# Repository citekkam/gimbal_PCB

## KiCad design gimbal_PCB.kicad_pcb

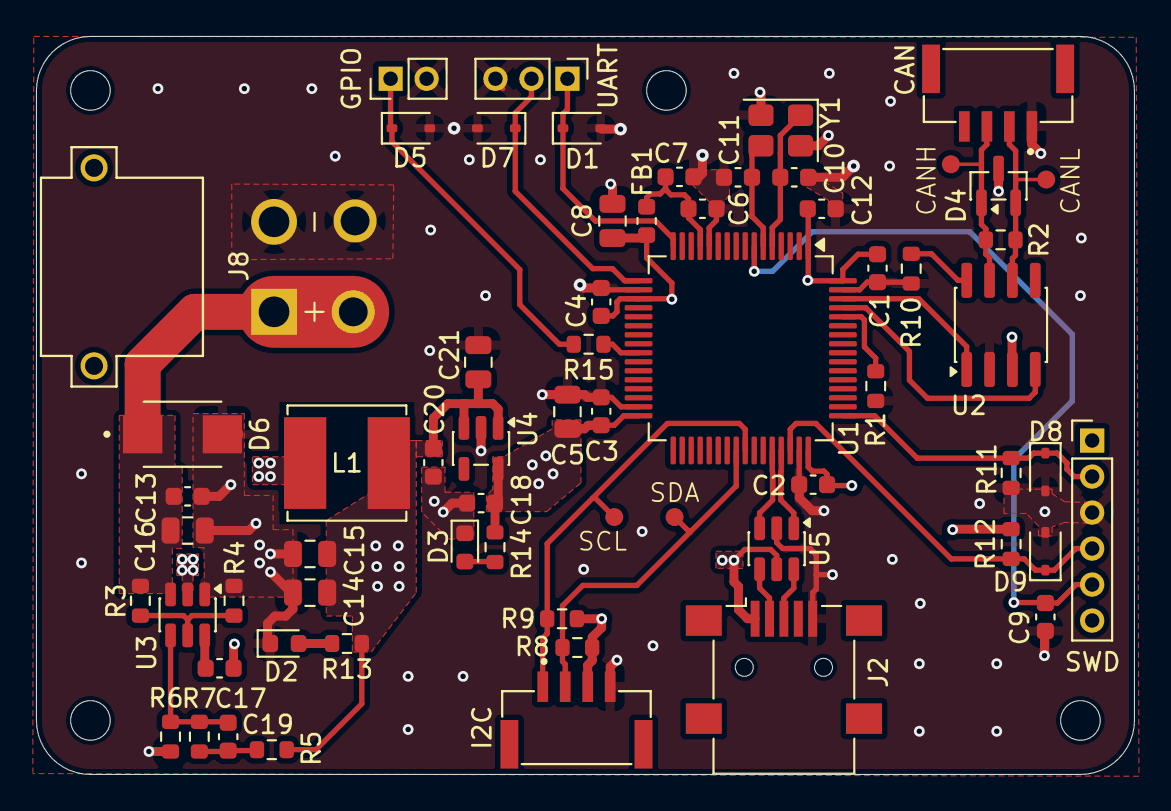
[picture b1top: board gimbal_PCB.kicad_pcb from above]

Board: 4 copper layers, 61.0 x 41.0 mm, 70 parts (0 on the bottom side), 33 nets.

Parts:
C1, C2, C3, C4, C9, C12: 100n; C_0603_1608Metric
C5, C16: 10u; C_0805_2012Metric
C6: 10n; C_0603_1608Metric
C7, C18, C20: 1u; C_0603_1608Metric
C8: 1u; C_0805_2012Metric
C10, C11: 8p; C_0603_1608Metric
C13, C17: 0.1u; C_0603_1608Metric
C14, C15: 22u; C_0805_2012Metric
C19: 75p; C_0603_1608Metric
C21: 1m; C_0805_2012Metric
CAN: Conn_01x04_Socket; JST_SM04B-GHS-TB_LF__SN_-
CANH: Conn_01x01_Pin; Test_point
CANL: Conn_01x01_Pin; Test_point
D1, D5, D7, D8, D9: PESD5V0S1UL; D_SOD-323
D2, D3: LED; LED_0603_1608Metric
D4: NUP2105L; SOT-23
D6: SMBJ28A; DIOM5436X244N
FB1: 120R; L_0603_1608Metric
GPIO: Conn_01x02_Pin; PinHeader_1x02_P2.00mm_Vertical
H3, H4, H5, H6: MountingHole; MountingHole_2.2mm_M2
I2C: Conn_01x04_Socket; JST_SM04B-GHS-TB_LF__SN_-
J2: USB_B_Mini; USB_Mini-B_Lumberg_2486_01_Horizontal
J5, J9: Conn_01x01_Socket; ODrive_PAD
J8: XT30PW-M; AMASS_XT30PW-M
L1: 10u; L_6.3x6.3_H3
R1: 10k; R_0603_1608Metric
R2: 120R; R_0603_1608Metric
R3: 511k; R_0603_1608Metric
R4: 105k; R_0603_1608Metric
R5: 49.9R; R_0603_1608Metric
R6: 13k3; R_0603_1608Metric
R7: 100k; R_0603_1608Metric
R8, R9: 2k2; R_0603_1608Metric
R10, R11, R12: 10K; R_0603_1608Metric
R13: 330R; R_0603_1608Metric
R14: 150R; R_0603_1608Metric
R15: 470R; R_0603_1608Metric
SCL: Conn_01x01_Pin; Test_point
SDA: Conn_01x01_Pin; Test_point
SWD: Conn_01x06_Socket; PinHeader_1x06_P2.00mm_Vertical
U1: STM32F446RETx; LQFP-64_10x10mm_P0.5mm
U2: SN65HVD230; SOIC-8_3.9x4.9mm_P1.27mm
U3: TPS54302; SOT-23-6
U4: ME6211C33M5; SOT-23-5
U5: USBLC6-2SC6; SOT-23-6
UART: Conn_01x03_Pin; PinHeader_1x03_P2.00mm_Vertical
Y1: 16MHz; Crystal_SMD_3225-4Pin_3.2x2.5mm

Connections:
+3.3V: C1.1, C2.1, C3.1, C4.1, C5.1, C8.1, C12.1, C18.1, FB1.1, R12.2, R14.1, U1.1 (VBAT), U1.19 (VDD), U1.32 (VDD), U1.48 (VDD), U1.64 (VDD), U2.3 (VCC), U4.5 (V_{OUT})
+3.3VA: C6.1, C7.1, FB1.2, U1.13 (VDDA)
+5V: C14.1, C15.1, C20.1, C21.1, I2C.3, J2.1 (VBUS), L1.2, R5.1, R8.1, R9.1, R13.1, U4.1 (V_{IN}), U4.3 (CE), U5.5 (VBUS)
/BOOT0: R1.2, U1.60 (BOOT0)
/CAN1_RX: U1.61 (PB8), U2.4 (R)
/CAN1_TX: U1.62 (PB9), U2.1 (D)
/GPIO_OUT: R15.1, U1.25 (PC5)
/HSE_IN: C10.1, U1.5 (PH0), Y1.1
/HSE_OUT: C11.1, U1.6 (PH1), Y1.3
/I2C3_SCL: I2C.1, R9.2, SCL.1, U1.41 (PA8)
/I2C3_SDA: I2C.2, R8.2, SDA.1, U1.40 (PC9)
/NRST: C9.1, SWD.5, U1.7 (NRST)
/SWCLK: D8.1 (K), R11.2, SWD.2, U1.49 (PA14)
/SWDIO: D9.1 (K), R12.1, SWD.4, U1.46 (PA13)
/USART_RX: D7.1 (K), U1.17 (PA3), UART.2
/USART_TX: D1.1 (K), U1.16 (PA2), UART.1
/USB_D+: U1.45 (PA12), U5.1 (I/O1)
/USB_D-: U1.44 (PA11), U5.3 (I/O2)
GND: C1.2, C2.2, C3.2, C4.2, C5.2, C6.2, C7.2, C8.2, C9.2, C10.2, C11.2, C12.2, C13.2, C14.2, C15.2, C16.2, C18.2, C20.2, C21.2, CAN.1, D1.2 (A), D2.1 (K), D3.1 (K), D4.3 (A), D5.2 (A), D6.A, D7.2 (A), D8.2 (A), D9.2 (A), GPIO.2, I2C.4, J2.5 (GND), J5.1, J8.N, R1.1, R4.2, R6.2, R10.2, R11.1, SWD.3, U1.12 (VSSA), U1.18 (VSS), U1.31 (VSS), U1.47 (VSS), U1.63 (VSS), U2.2 (GND), U3.1 (GND), U4.2 (V_{SS}), U5.2 (GND), UART.3, Y1.2 (G), Y1.4 (G)
unnamed: C19.1, R5.2, R7.1
unnamed: D2.2 (A), R13.2
unnamed: D3.2 (A), R14.2
unnamed: D5.1 (K), GPIO.1, R15.2
unnamed: CAN.2, CANL.1, D4.2 (K), R2.2, U2.6 (CANL)
unnamed: CAN.3, CANH.1, D4.1 (K), R2.1, U2.7 (CANH)
unnamed: J2.3 (D+), U5.6 (I/O1)
unnamed: J2.2 (D-), U5.4 (I/O2)
unnamed: R10.1, U2.8 (Rs)
unnamed: C17.1, U3.6 (BOOT)
unnamed: R3.2, R4.1, U3.5 (EN)
unnamed: C19.2, R6.1, R7.2, U3.4 (FB)
unnamed: C17.2, L1.1, U3.2 (SW)
napeti_z_baterie: C13.1, C16.1, D6.C, J8.P, J9.1, R3.1, U3.3 (VIN)

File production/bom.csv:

Designator,Footprint,Quantity,Value,LCSC Part #
"C1, C12, C2, C3, C4, C9",0603,6,100n,
"C10, C11",0603,2,8p,
"C13, C17",0603,2,0.1u,
"C14, C15",0805,2,22u,
"C16, C5",0805,2,10u,
"C18, C20, C7",0603,3,1u,
C19,0603,1,75p,
C21,C_Radial_D8.0mm_H11.5mm_P3.50mm,1,1m,
C6,0603,1,10n,
C8,0805,1,1u,
"CAN, I2C",JST_SM04B-GHS-TB_LF__SN_-,2,Conn_01x04_Socket,
"CANH, CANL, SCL, SDA",Test_point,4,Conn_01x01_Pin,
"D1, D5, D7, D8, D9",D_SOD-323,5,PESD5V0S1UL,
"D2, D3",0603,2,LED,
D4,SOT-23,1,NUP2105L,
D6,DIOM5436X244N,1,SMBJ28A,
"FB1, R2",0603,2,120R,
GPIO,PinHeader_1x02_P2.00mm_Vertical,1,Conn_01x02_Pin,
J2,USB_Mini-B_Lumberg_2486_01_Horizontal,1,USB_B_Mini,
"J5, J9",ODrive_PAD,2,Conn_01x01_Socket,
J8,AMASS_XT30PW-M,1,XT30PW-M,
L1,L_6.3x6.3_H3,1,10u,
"R1, R10, R11, R12",0603,4,10k,
R13,0603,1,330R,
R14,0603,1,150R,
R15,0603,1,470R,
R16,1206,1,500m,
R3,0603,1,511k,
R4,0603,1,105k,
R5,0603,1,49.9R,
R6,0603,1,13k3,
R7,0603,1,100k,
"R8, R9",0603,2,2k2,
SWD,PinHeader_1x06_P2.00mm_Vertical,1,Conn_01x06_Socket,
U1,LQFP-64_10x10mm_P0.5mm,1,STM32F446RETx,
U2,SOIC-8_3.9x4.9mm_P1.27mm,1,SN65HVD230,
U3,SOT-23-6,1,TPS54302,
U4,SOT-23-5,1,ME6211C33M5,
U5,SOT-23-6,1,USBLC6-2SC6,
UART,PinHeader_1x03_P2.00mm_Vertical,1,Conn_01x03_Pin,
Y1,Crystal_SMD_3225-4Pin_3.2x2.5mm,1,16MHz,

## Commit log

2026-02-11 Komplementace a finalni upravy
2026-02-12 Komplementace a finalni upravy_V2
2026-02-12 Komplementace a finalni upravy_V3
2026-02-12 Komplementace a finalni upravy_V4
2026-02-13 Komplementace a finalni upravy_V5
2026-02-13 Komplementace a finalni upravy_V6
2026-02-13 Komplementace a finalni upravy_V7
2026-03-03 latest version
